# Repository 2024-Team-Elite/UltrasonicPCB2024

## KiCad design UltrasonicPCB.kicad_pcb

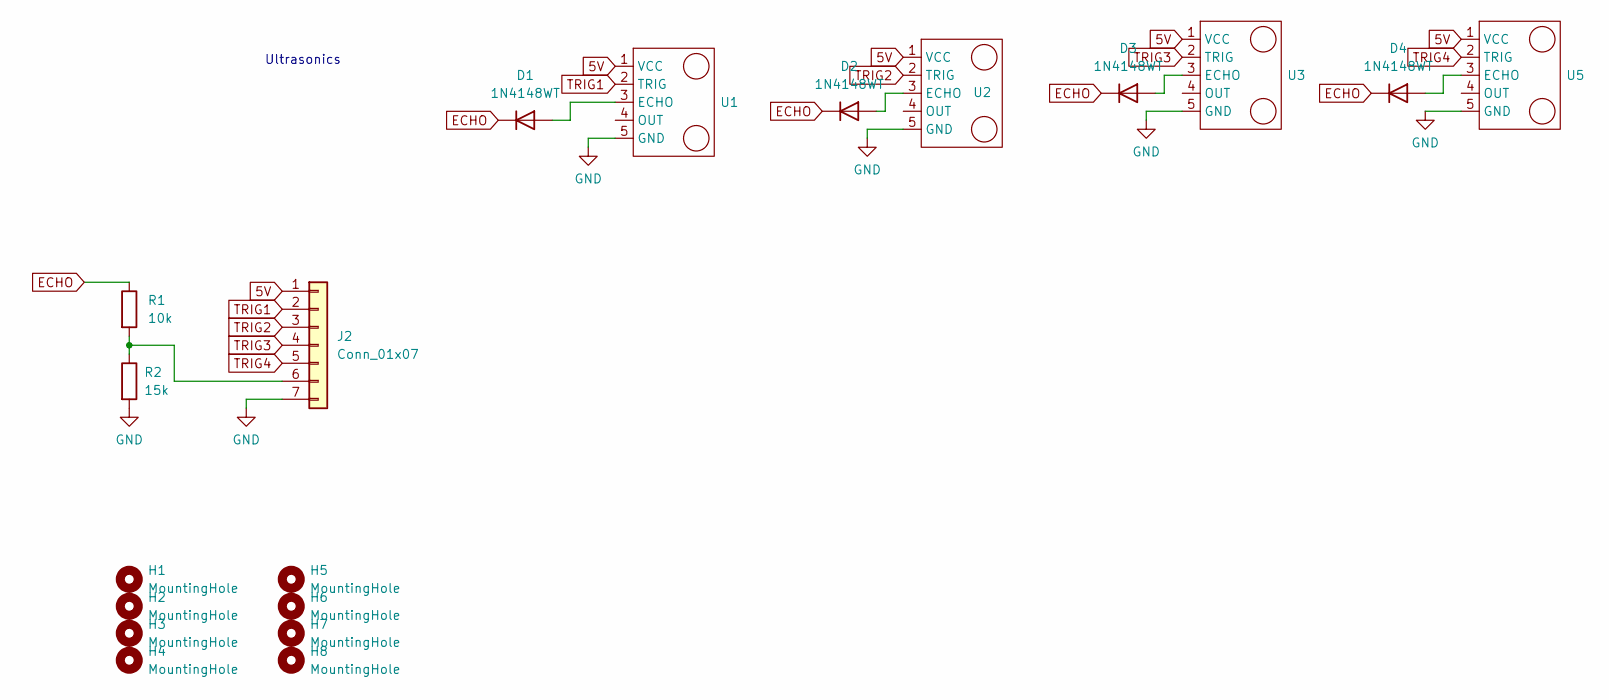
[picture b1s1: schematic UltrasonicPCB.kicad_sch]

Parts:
D1, D2, D3, D4: 1N4148WT; D_SOD-123
H1, H2, H3, H4, H5, H6, H7, H8: MountingHole; MountingHole_3.2mm_M3_DIN965_Pad
J2: Conn_01x07; IDC-Header_2x04_P2.54mm_Vertical
R1: 10k; R_0805_2012Metric_Pad1.20x1.40mm_HandSolder
R2: 15k; R_0805_2012Metric_Pad1.20x1.40mm_HandSolder
U1, U2, U3, U5: PinHeader_1x05_P2.54mm_Vertical

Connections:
5V: J2.1, U1.1 (VCC), U2.1 (VCC), U3.1 (VCC), U5.1 (VCC)
ECHO: D1.1 (K), D2.1 (K), D3.1 (K), D4.1 (K), R1.1
GND: J2.7, R2.2, U1.5 (GND), U2.5 (GND), U3.5 (GND), U5.5 (GND)
unnamed: D1.2 (A), U1.3 (ECHO)
unnamed: D2.2 (A), U2.3 (ECHO)
unnamed: D3.2 (A), U3.3 (ECHO)
unnamed: D4.2 (A), U5.3 (ECHO)
unnamed: J2.6, R1.2, R2.1
TRIG1: J2.2, U1.2 (TRIG)
TRIG2: J2.3, U2.2 (TRIG)
TRIG3: J2.4, U3.2 (TRIG)
TRIG4: J2.5, U5.2 (TRIG)

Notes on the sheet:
Ultrasonics

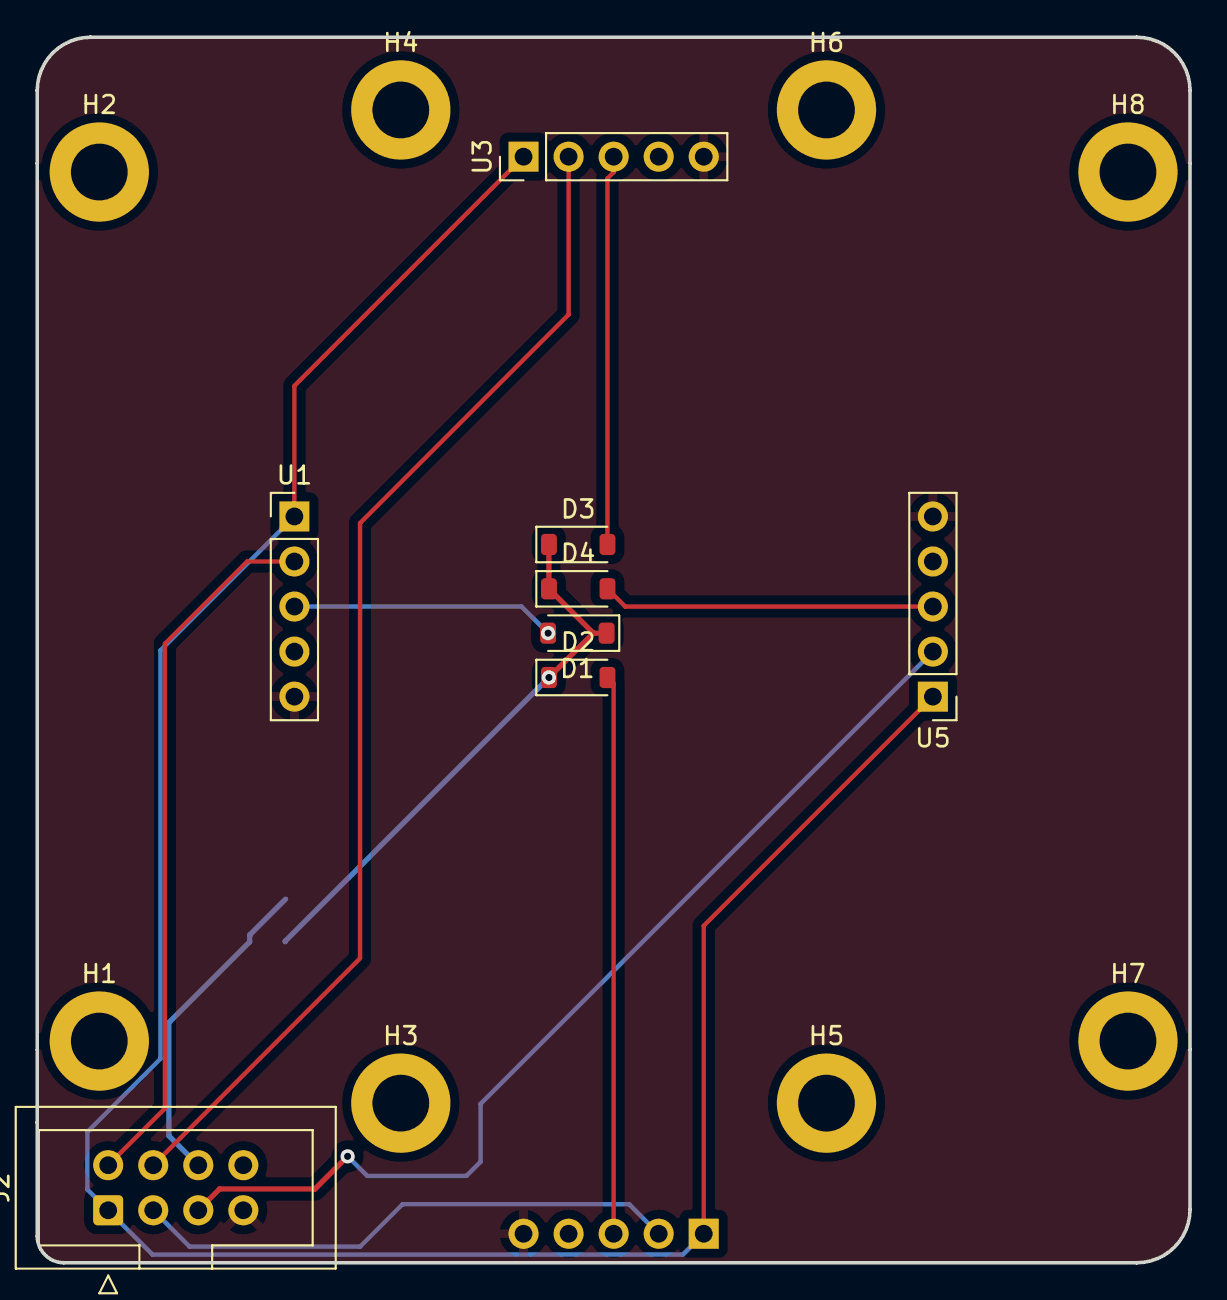
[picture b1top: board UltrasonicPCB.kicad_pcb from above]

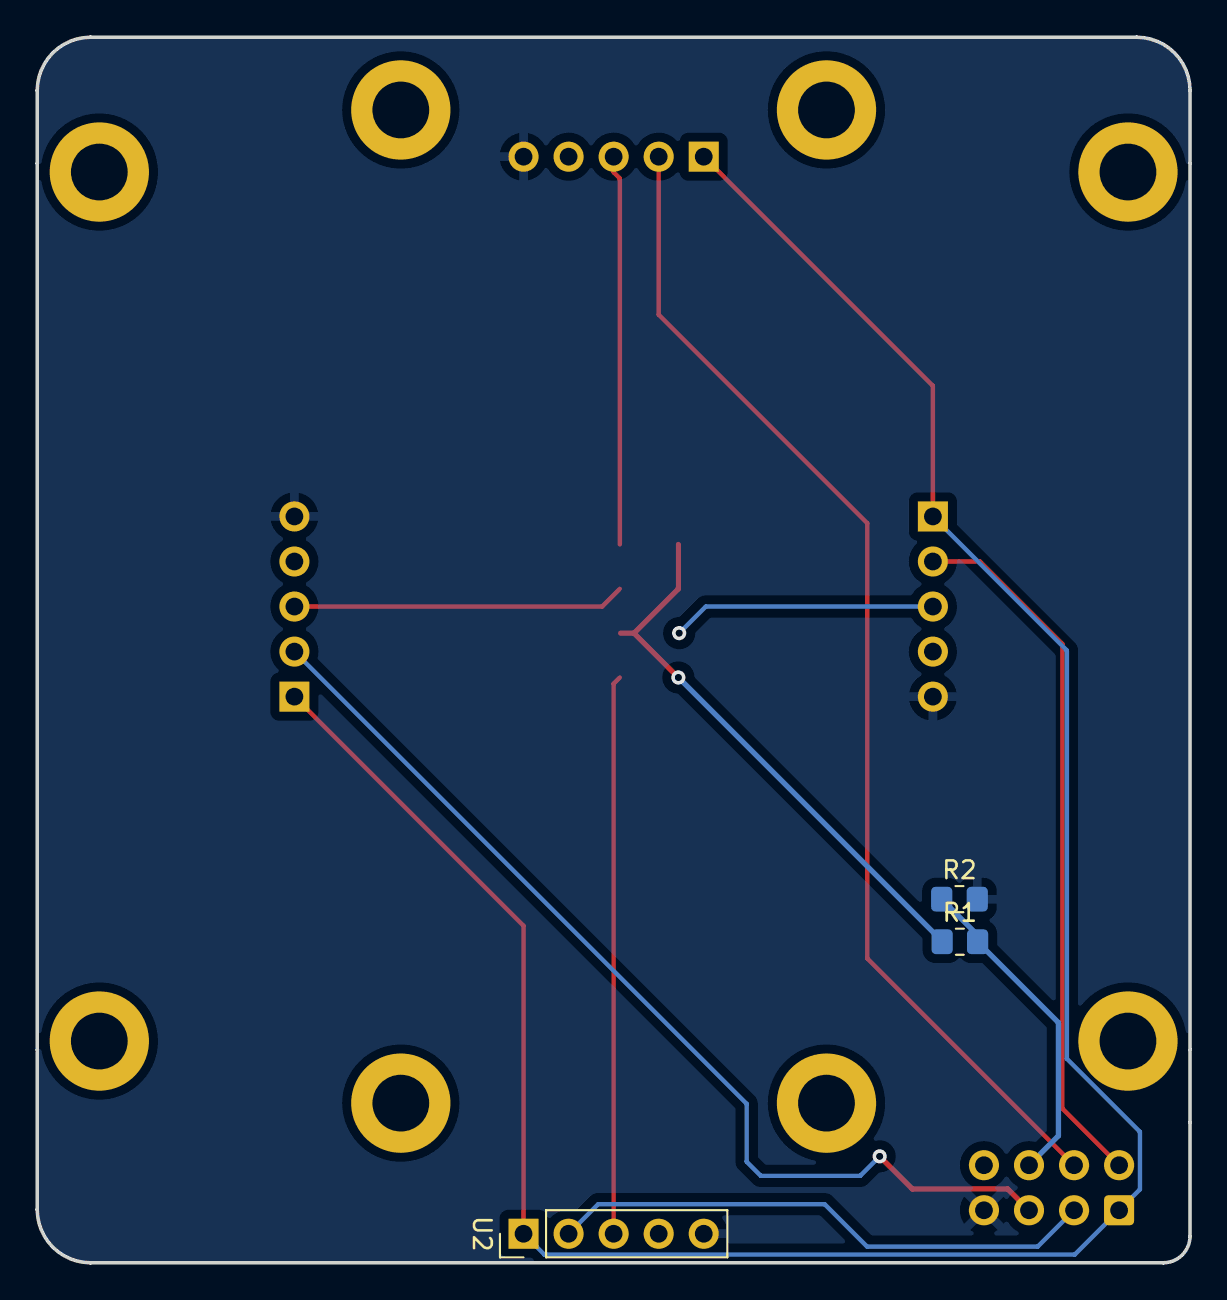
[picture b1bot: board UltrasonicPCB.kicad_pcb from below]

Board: 2 copper layers, 65.0 x 69.1 mm, 19 parts (3 on the bottom side), 12 nets.

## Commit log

2024-03-03 Finished
2024-03-07 Updated with 1 echo
2024-04-13 Changed Outline
2024-04-14 2nd Revision
2024-04-14 M3 screwhole fix
2024-04-15 Fixed Ultrasonic Sides
2024-04-15 Done
2024-04-15 Remake the PCB
2024-04-15 Cleaned Locks
2024-04-26 Moved Ultrasonics again
2024-04-26 continuation
